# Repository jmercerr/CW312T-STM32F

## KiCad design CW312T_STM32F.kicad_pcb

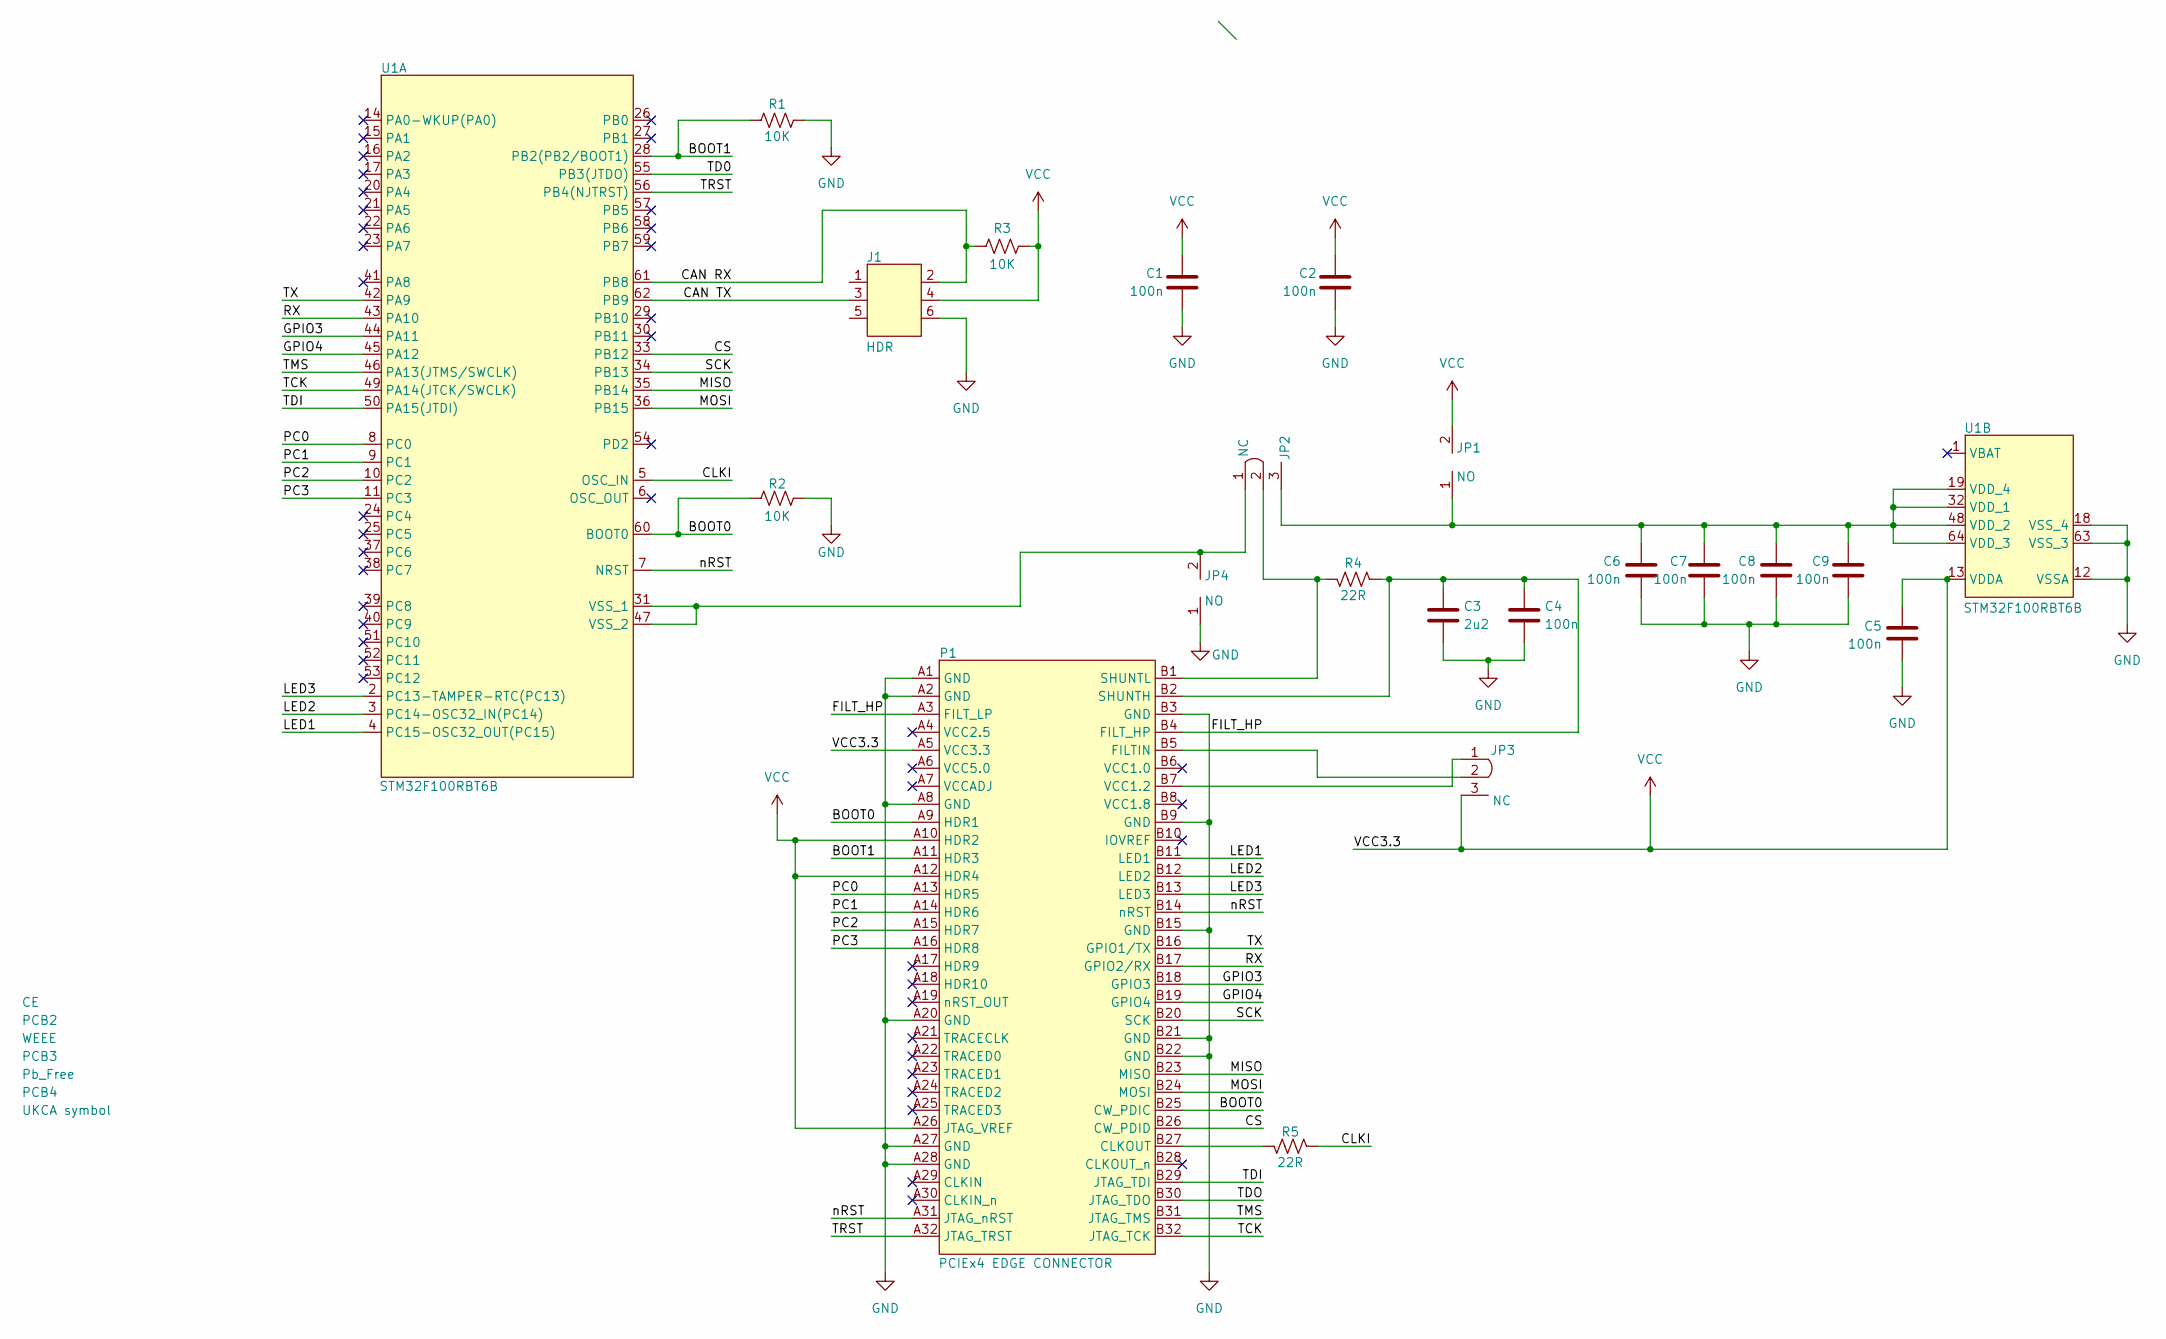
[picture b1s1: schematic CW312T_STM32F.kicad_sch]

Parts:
C1, C2, C4, C5, C6, C7, C8, C9: CAP_100n_50V_0603; C_0603_1608Metric; Manufacturer Part Number C0603C104M5RACTU
C3: CAP_2u2_16V_0603; C_0603_1608Metric; Manufacturer Part Number C0603C225K4PAC7867
J1: HDR_6_2.54; PinHeader_2x03_P1.00mm_Vertical; Manufacturer Part Number PH2-06-UA
JP1, JP4: SolderJumper-2_P1.3mm_Open_Pad1.0x1.5mm
JP2, JP3: SolderJumper-3_P1.3mm_Bridged2Bar12_Pad1.0x1.5mm
P1: PCIEx4 EDGE CONNECTOR; CW312_Template
PCB1: CE; CE-Logo_8.5x6mm_SilkScreen
PCB2: WEEE; WEEE-Logo_5.6x8mm_SilkScreen
PCB3: Pb_Free; Pb_Free_8.0x8.0mm_SilkScreen
PCB4: UKCA symbol; UKCA-Logo_8x8mm_SilkScreen
R1, R2, R3: 10K; R_0603_1608Metric; Manufacturer Part Number RC0603JR-0710KL
R4: 22R_0603; R_0603_1608Metric; Manufacturer Part Number RC0603JR-0722RL
R5: 51R_0603; R_0603_1608Metric; Manufacturer Part Number RC0603JR-0751RL
U1: STM32F100RBT6B; TQFP-64_10x10mm_P0.5mm; Manufacturer Part Number STM32F100RBT6B

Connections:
/BOOT0: P1.A9 (HDR1), P1.B25 (CW_PDIC), R2.1, U1.60 (BOOT0)
/BOOT1: P1.A11 (HDR3), R1.1, U1.28 (PB2(PB2/BOOT1))
/CAN RX: J1.2, R3.1, U1.61 (PB8)
/CAN TX: J1.3, U1.62 (PB9)
/CLKI: R5.2, U1.5 (OSC_IN)
/CS: P1.B26 (CW_PDID), U1.33 (PB12)
/FILT_HP: C3.1, C4.1, P1.A3 (FILT_LP), P1.B2 (SHUNTH), P1.B4 (FILT_HP), R4.2
/GPIO3: P1.B18 (GPIO3), U1.44 (PA11)
/GPIO4: P1.B19 (GPIO4), U1.45 (PA12)
/LED1: P1.B11 (LED1), U1.4 (PC15-OSC32_OUT(PC15))
/LED2: P1.B12 (LED2), U1.3 (PC14-OSC32_IN(PC14))
/LED3: P1.B13 (LED3), U1.2 (PC13-TAMPER-RTC(PC13))
/MISO: P1.B23 (MISO), U1.35 (PB14)
/MOSI: P1.B24 (MOSI), U1.36 (PB15)
/PC0: P1.A13 (HDR5), U1.8 (PC0)
/PC1: P1.A14 (HDR6), U1.9 (PC1)
/PC2: P1.A15 (HDR7), U1.10 (PC2)
/PC3: P1.A16 (HDR8), U1.11 (PC3)
/RX: P1.B17 (GPIO2/RX), U1.43 (PA10)
/SCK: P1.B20 (SCK), U1.34 (PB13)
/TCK: P1.B32 (JTAG_TCK), U1.49 (PA14(JTCK/SWCLK))
/TD0: U1.55 (PB3(JTDO))
/TDI: P1.B29 (JTAG_TDI), U1.50 (PA15(JTDI))
/TDO: P1.B30 (JTAG_TDO)
/TMS: P1.B31 (JTAG_TMS), U1.46 (PA13(JTMS/SWCLK))
/TRST: P1.A32 (JTAG_TRST), U1.56 (PB4(NJTRST))
/TX: P1.B16 (GPIO1/TX), U1.42 (PA9)
/nRST: P1.A31 (JTAG_nRST), P1.B14 (nRST), U1.7 (NRST)
GND: C1.2, C2.2, C3.2, C4.2, C5.2, C6.2, C7.2, C8.2, C9.2, J1.6, JP4.1, P1.A1 (GND), P1.A2 (GND), P1.A8 (GND), P1.A20 (GND), P1.A27 (GND), P1.A28 (GND), P1.B3 (GND), P1.B9 (GND), P1.B15 (GND), P1.B21 (GND), P1.B22 (GND), R1.2, R2.2, U1.12 (VSSA), U1.18 (VSS_4), U1.63 (VSS_3)
unnamed: P1.B27 (CLKOUT), R5.1
unnamed: JP3.2, P1.B5 (FILTIN)
unnamed: JP2.2, P1.B1 (SHUNTL), R4.1
unnamed: JP3.1, P1.B7 (VCC1.2)
unnamed: JP2.1, JP4.2, U1.31 (VSS_1), U1.47 (VSS_2)
unnamed: C6.1, C7.1, C8.1, C9.1, JP1.1, JP2.3, U1.19 (VDD_4), U1.32 (VDD_1), U1.48 (VDD_2), U1.64 (VDD_3)
VCC: C1.1, C2.1, C5.1, J1.4, JP1.2, JP3.3, P1.A5 (VCC3.3), P1.A10 (HDR2), P1.A12 (HDR4), P1.A26 (JTAG_VREF), R3.2, U1.13 (VDDA)

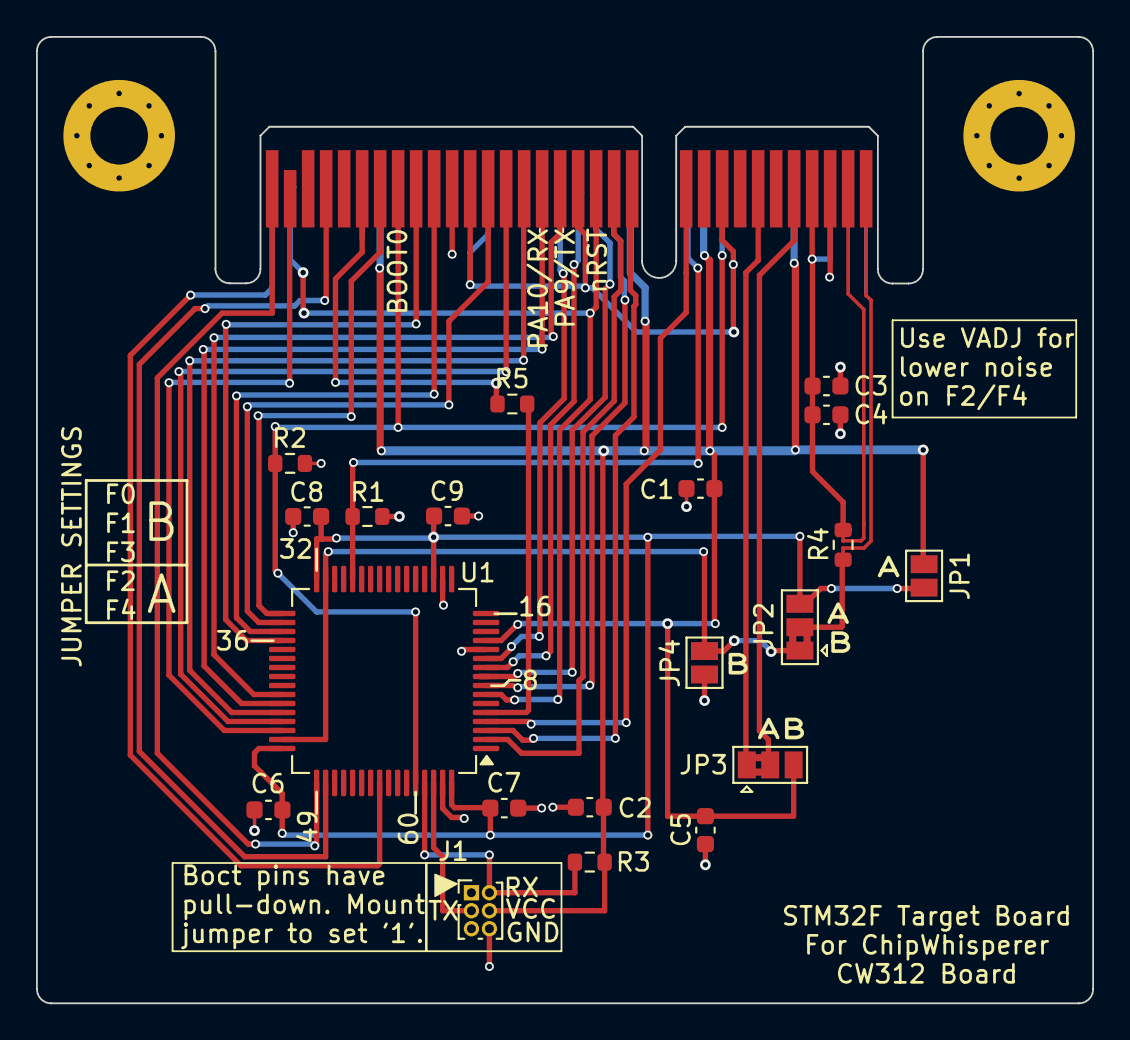
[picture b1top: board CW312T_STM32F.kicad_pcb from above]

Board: 2 copper layers, 58.7 x 53.7 mm, 25 parts (0 on the bottom side), 34 nets.

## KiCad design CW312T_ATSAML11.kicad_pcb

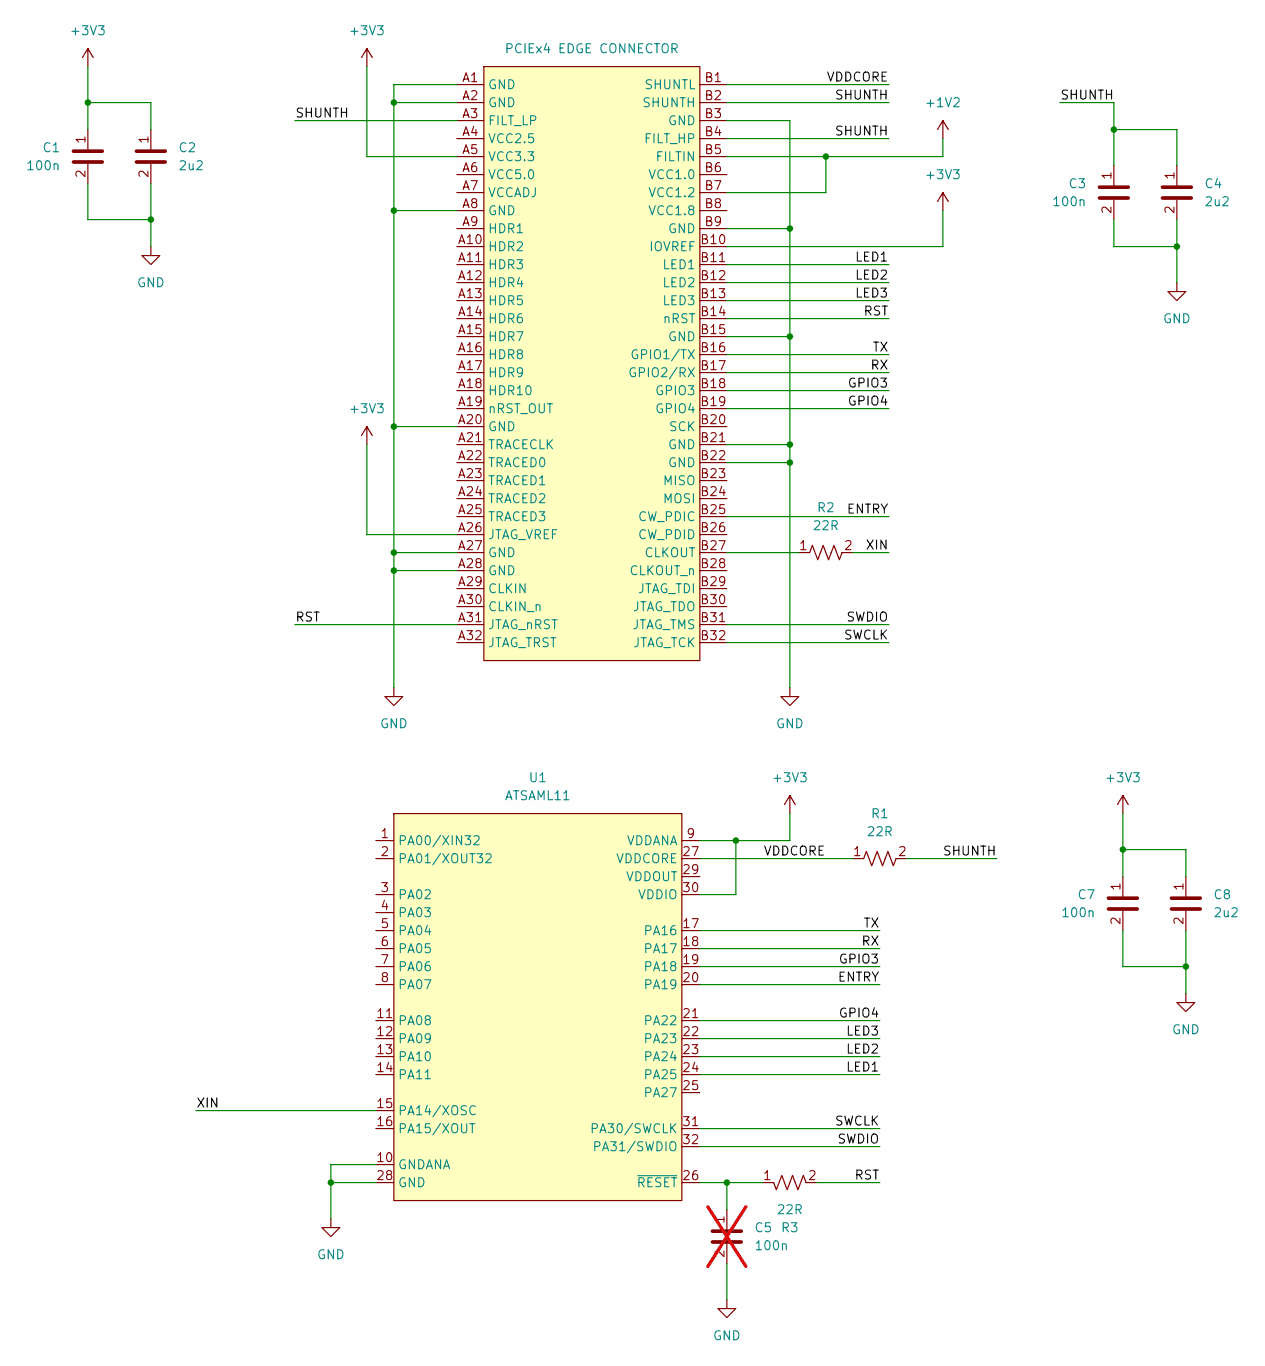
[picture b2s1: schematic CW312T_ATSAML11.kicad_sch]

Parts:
C1, C3, C7: CAP_100n_50V_0603; C_0603_1608Metric; Manufacturer Part Number C0603C104M5RACTU
C2, C4, C8: CAP_2u2_16V_0603; C_0603_1608Metric; Manufacturer Part Number C0603C225K4PAC7867
C5: CAP_100n_50V_0603; C_0603_1608Metric; Manufacturer Part Number C0603C104M5RACTU; not fitted
P1: PCIEx4 EDGE CONNECTOR; CW312_Template
R1, R2, R3: 22R_0603; R_0603_1608Metric; Manufacturer Part Number RC0603JR-0722RL
U1: ATSMAL11E16A-AU; TQFP-32_7x7mm_P0.8mm; Manufacturer Part Number ATSAML11E16A-AU

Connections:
+1V2: P1.B5 (FILTIN), P1.B7 (VCC1.2)
+3V3: C1.1, C2.1, C7.1, C8.1, P1.A5 (VCC3.3), P1.A26 (JTAG_VREF), P1.B10 (IOVREF), U1.9 (VDDANA), U1.30 (VDDIO)
/ENTRY: P1.B25 (CW_PDIC), U1.20 (PA19)
/GPIO3: P1.B18 (GPIO3), U1.19 (PA18)
/GPIO4: P1.B19 (GPIO4), U1.21 (PA22)
/LED1: P1.B11 (LED1), U1.24 (PA25)
/LED2: P1.B12 (LED2), U1.23 (PA24)
/LED3: P1.B13 (LED3), U1.22 (PA23)
/RST: P1.A31 (JTAG_nRST), P1.B14 (nRST), R3.2
/RX: P1.B17 (GPIO2/RX), U1.18 (PA17)
/SHUNTH: C3.1, C4.1, P1.A3 (FILT_LP), P1.B2 (SHUNTH), P1.B4 (FILT_HP), R1.2
/SWCLK: P1.B32 (JTAG_TCK), U1.31 (PA30/SWCLK)
/SWDIO: P1.B31 (JTAG_TMS), U1.32 (PA31/SWDIO)
/TX: P1.B16 (GPIO1/TX), U1.17 (PA16)
/VDDCORE: P1.B1 (SHUNTL), R1.1, U1.27 (VDDCORE)
/XIN: R2.2, U1.15 (PA14/XOSC)
GND: C1.2, C2.2, C3.2, C4.2, C5.2, C7.2, C8.2, P1.A1 (GND), P1.A2 (GND), P1.A8 (GND), P1.A20 (GND), P1.A27 (GND), P1.A28 (GND), P1.B3 (GND), P1.B9 (GND), P1.B15 (GND), P1.B21 (GND), P1.B22 (GND), U1.10 (GNDANA), U1.28 (GND)
unnamed: P1.B27 (CLKOUT), R2.1
unnamed: C5.1, R3.1, U1.26 (~RESET)

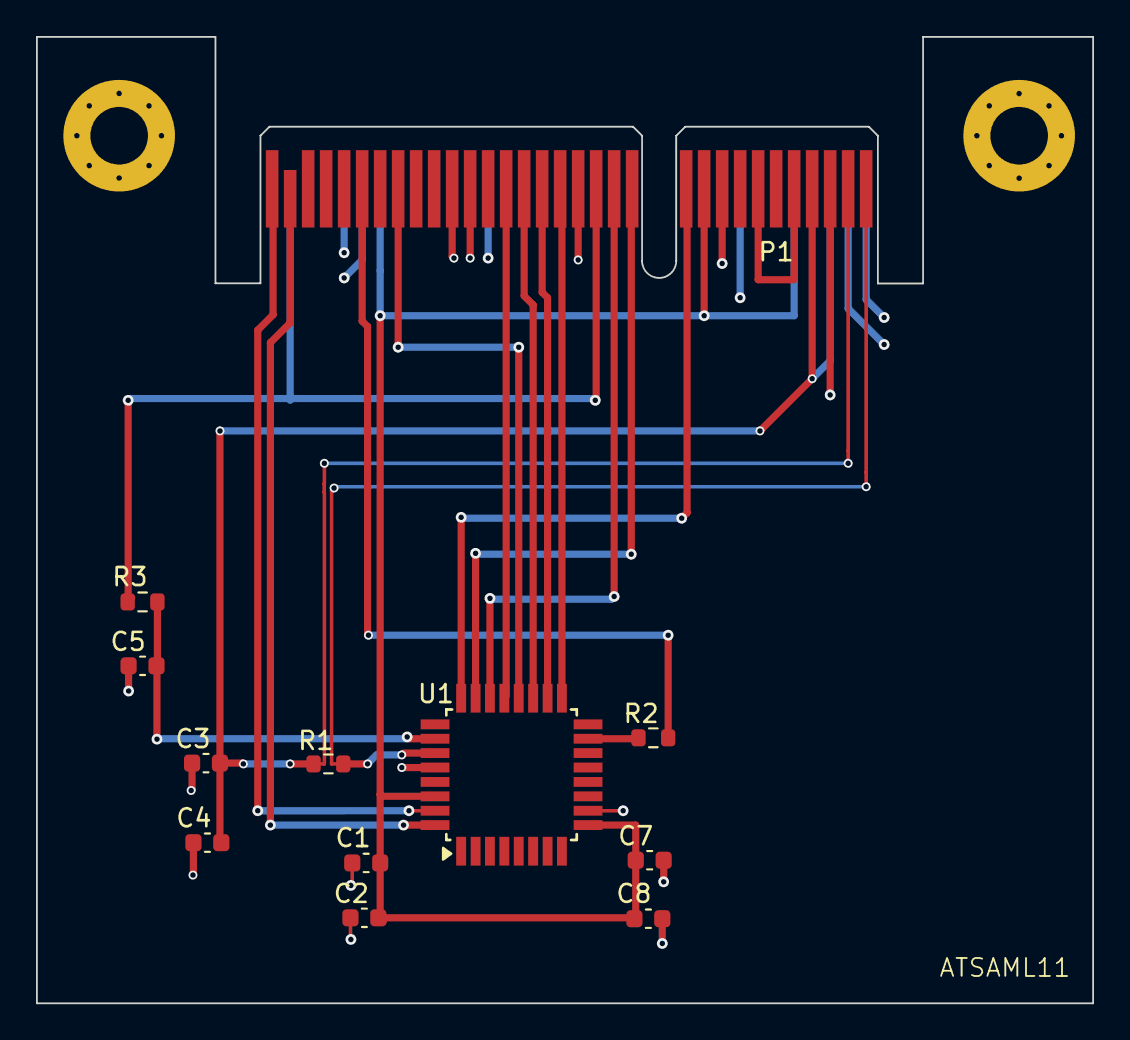
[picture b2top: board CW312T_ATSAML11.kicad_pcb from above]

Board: 2 copper layers, 58.7 x 53.7 mm, 12 parts (0 on the bottom side), 19 nets.

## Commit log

2024-10-28 Routing of shunt resistor should have been prioritized
2024-10-28 added product name on board
2024-11-01 uploading stm32f files
2024-11-13 updated CW312T-STM32F1 design
2024-11-13 Updated CW312T_STM32F Design
2024-11-21 updated design - fixed connections, got rid of visible pin numbers on passives, updated silkscreen
2024-11-22 updated cw312t template and production files
2024-12-19 updated schematic and pcb after library reorganization, and updated pin header to include proper footprint
